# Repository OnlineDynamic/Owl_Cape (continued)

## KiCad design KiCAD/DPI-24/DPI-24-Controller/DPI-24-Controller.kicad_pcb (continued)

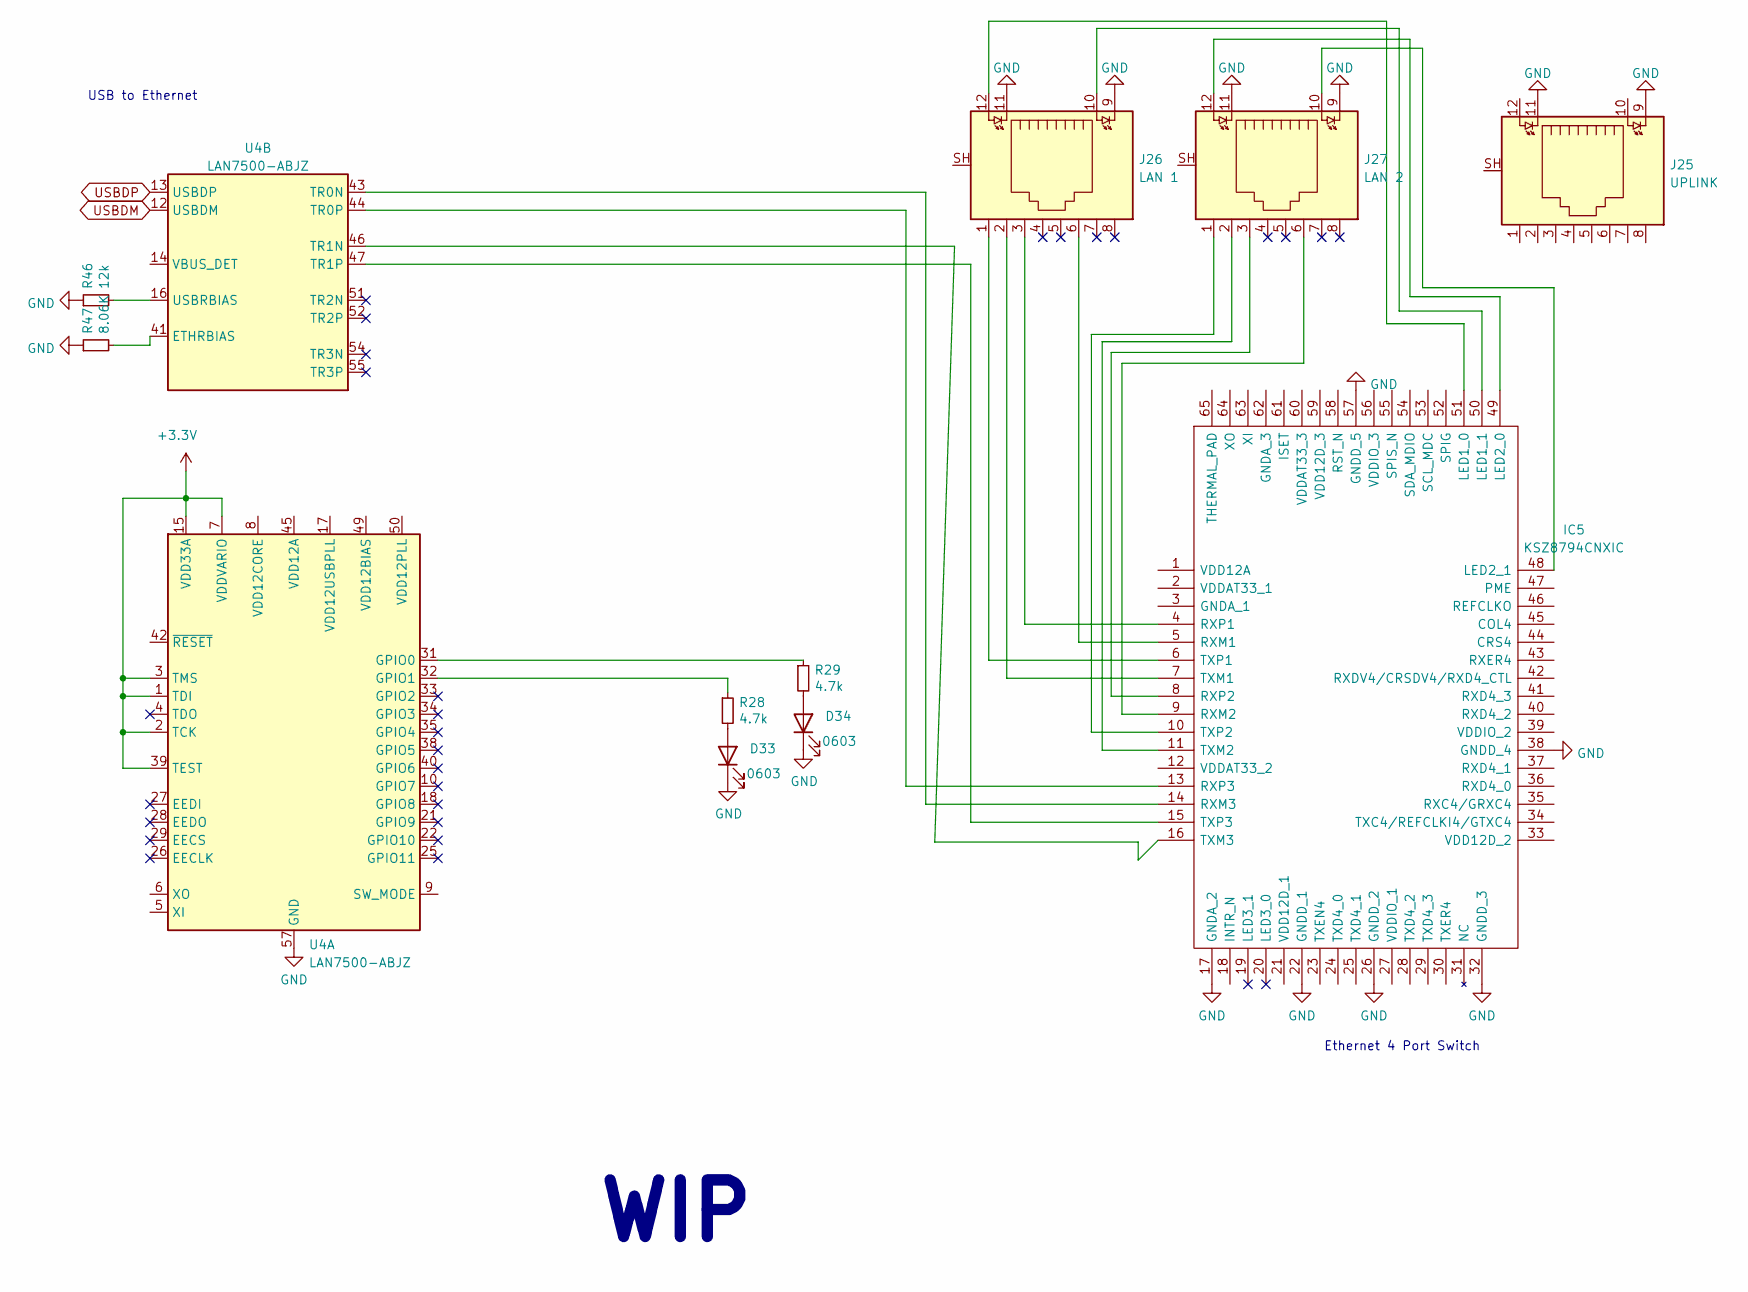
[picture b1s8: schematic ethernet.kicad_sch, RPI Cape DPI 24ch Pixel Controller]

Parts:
D33, D34: 0603; LED_0603_1608Metric
IC5: KSZ8794CNXIC; QFN40P800X800X90-65N; Mouser Part Number 998-KSZ8794CNXIC
J25: UPLINK; RJ45_BEL_SS74301-00x_Vertical
J26: LAN 1; RJ45_BEL_SS74301-00x_Vertical
J27: LAN 2; RJ45_BEL_SS74301-00x_Vertical
R28, R29: 4.7k; R_0805_2012Metric
R46: 12k; R_0805_2012Metric
R47: 8.06K; R_0805_2012Metric
U4: LAN7500-ABJZ; QFN-56-1EP_8x8mm_P0.5mm_EP5.9x5.9mm

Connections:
unnamed: D33.2 (A), R28.2
unnamed: D34.2 (A), R29.2
unnamed: IC5.4 (RXP1), J26.3
unnamed: IC5.5 (RXM1), J26.6
unnamed: IC5.6 (TXP1), J26.1
unnamed: IC5.7 (TXM1), J26.2
unnamed: IC5.8 (RXP2), J27.3
unnamed: IC5.9 (RXM2), J27.6
unnamed: IC5.10 (TXP2), J27.1
unnamed: IC5.11 (TXM2), J27.2
unnamed: IC5.13 (RXP3), U4.44 (TR0P)
unnamed: IC5.14 (RXM3), U4.43 (TR0N)
unnamed: IC5.15 (TXP3), U4.47 (TR1P)
unnamed: IC5.16 (TXM3), U4.46 (TR1N)
unnamed: IC5.48 (LED2_1), J27.10
unnamed: IC5.49 (LED2_0), J27.12
unnamed: IC5.50 (LED1_1), J26.10
unnamed: IC5.51 (LED1_0), J26.12
unnamed: R28.1, U4.32 (GPIO1)
unnamed: R29.1, U4.31 (GPIO0)
unnamed: R46.2, U4.16 (USBRBIAS)
unnamed: R47.2, U4.41 (ETHRBIAS)
unnamed: U4.8 (VDD12CORE), U4.11 (VDD12CORE), U4.20 (VDD12CORE), U4.23 (VDD12CORE), U4.30 (VDD12CORE), U4.36 (VDD12CORE)
unnamed: U4.45 (VDD12A), U4.48 (VDD12A), U4.53 (VDD12A), U4.56 (VDD12A)
USBDM: U4.12 (USBDM)
USBDP: U4.13 (USBDP)

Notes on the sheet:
USB to Ethernet
Ethernet 4 Port Switch
WIP

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
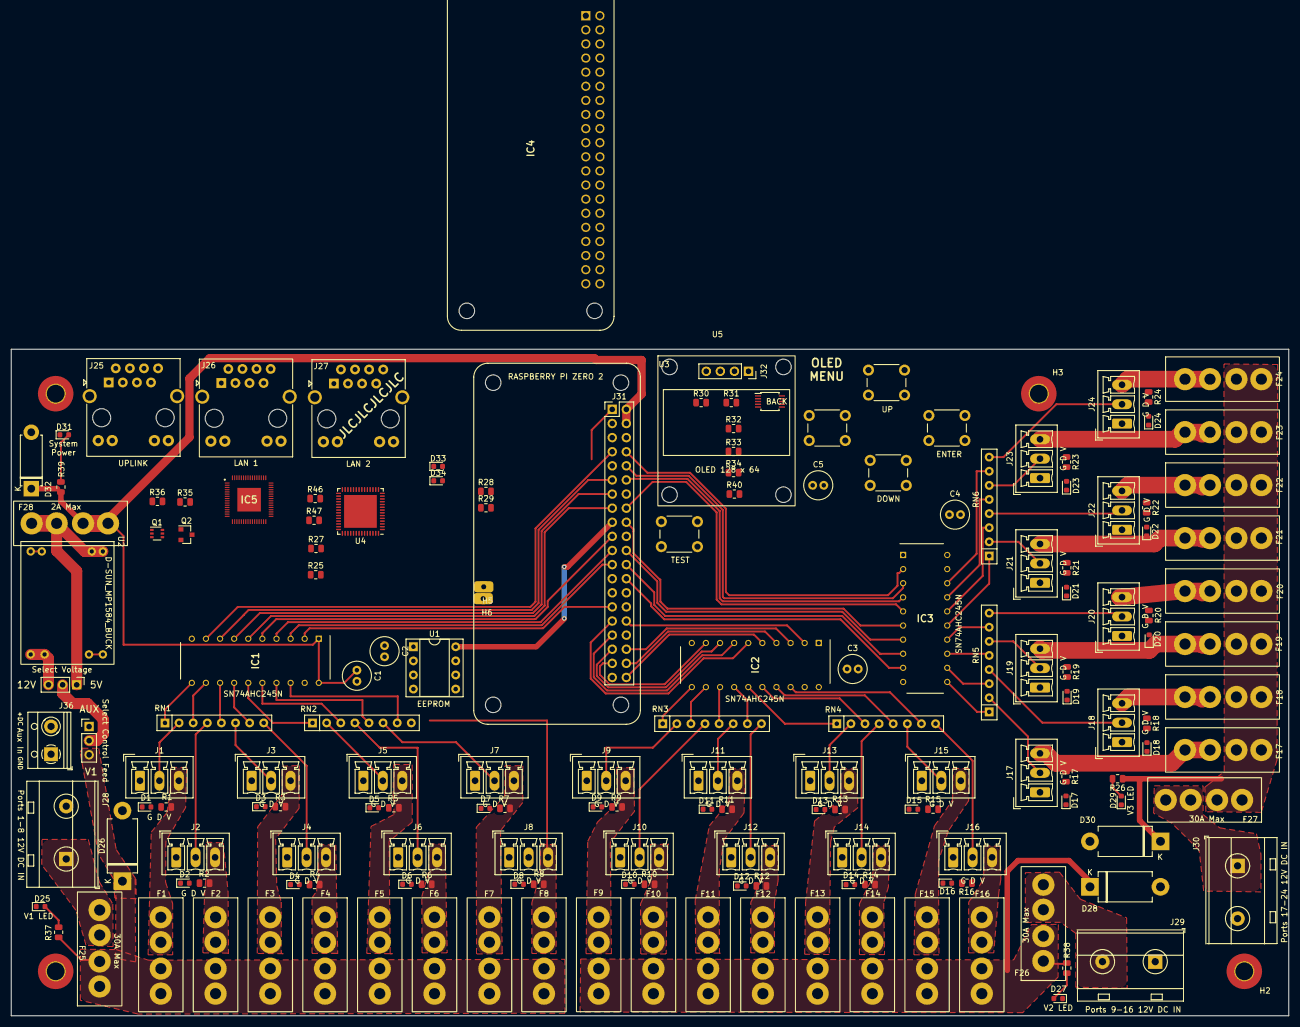
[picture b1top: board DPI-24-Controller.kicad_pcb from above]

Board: 2 copper layers, 230.0 x 120.0 mm, 173 parts (0 on the bottom side), 176 nets.

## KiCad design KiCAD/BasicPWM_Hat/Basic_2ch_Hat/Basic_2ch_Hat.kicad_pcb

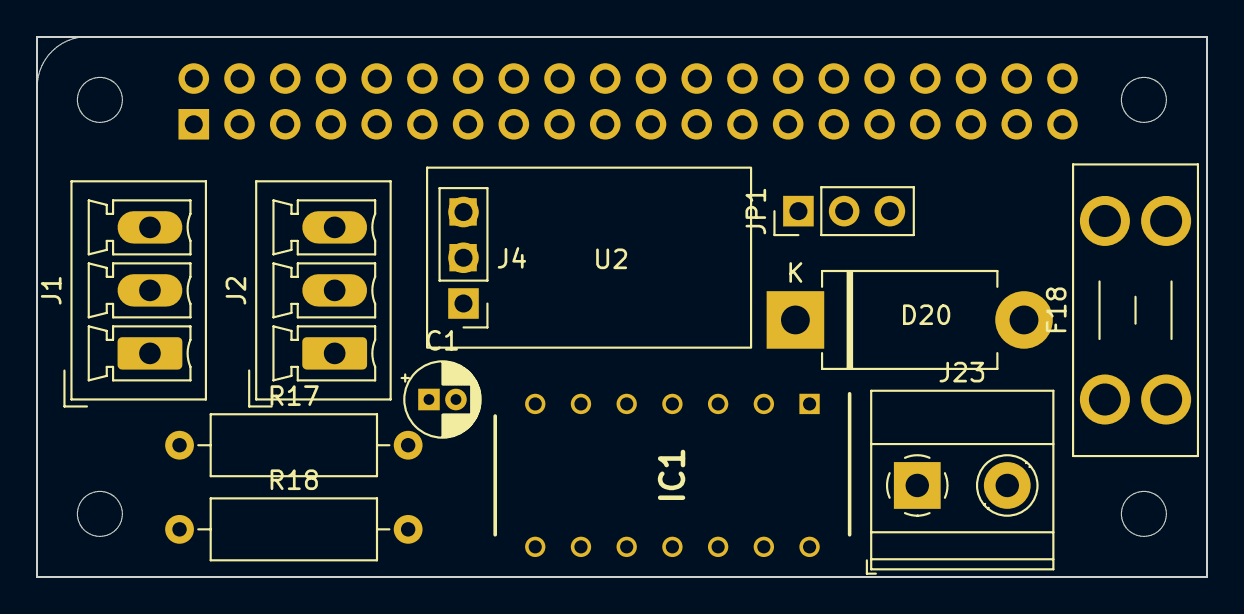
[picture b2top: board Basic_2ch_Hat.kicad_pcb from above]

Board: 2 copper layers, 65.0 x 30.0 mm, 17 parts (1 on the bottom side), 13 nets, no tracks yet.

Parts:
C1: 0.1uF; CP_Radial_D4.0mm_P1.50mm
D20: SB5100; D_DO-201AD_P12.70mm_Horizontal
F18: 30A Max; Fuseholder_Blade_Mini_Keystone_3568
H1, H2, H3, H4: MountingHole; MountingHole_2.5mm
IC1: SN74HC126N; DIP794W53P254L1930H508Q14N
J1, J2: G D V; PhoenixContact_MCV_1,5_3-G-3.5_1x03_P3.50mm_Vertical
J3: Conn_02x20_Odd_Even_MountingPin; PinSocket_2x20_P2.54mm_Vertical
J4: Conn_01x03; PinHeader_1x03_P2.54mm_Vertical
J23: DC In; TerminalBlock_Phoenix_MKDS-1,5-2_1x02_P5.00mm_Horizontal
JP1: 5V / 12V; PinHeader_1x03_P2.54mm_Vertical
R17, R18: 33; R_Axial_DIN0309_L9.0mm_D3.2mm_P12.70mm_Horizontal
U2: DC DC_BUCK Module; DC DC BUCK MODULE

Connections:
+3V3: J3.1, J3.17
+5V: C1.1, IC1.14 (VCC)
DATA1: IC1.2 (1A), J3.32
DATA2: IC1.5 (2A), J3.33
GND: C1.2, D20.2 (A), IC1.1 (1OE), IC1.4 (2OE), IC1.7 (GND), IC1.10 (3OE), IC1.13 (4OE), J1.1, J2.1, J3.6, J3.9, J3.14, J3.20, J3.25, J3.30, J3.34, J3.39, J4.2, J23.1
unnamed: IC1.3 (1Y), R18.2
unnamed: IC1.6 (2Y), R17.2
unnamed: J1.2, R18.1
unnamed: J2.2, R17.1
V1: F18.1, J23.2
V5: J3.2, J3.4, J4.3, JP1.1 (A)
V12: J4.1, JP1.3 (B)
VIN1: D20.1 (K), F18.2, J1.3, J2.3, JP1.2 (C)

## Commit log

2022-03-18 typos
2022-03-18 inital commit of KiCAD WIP
2022-03-18 upload
2022-03-18 research upload
2022-03-18 updates to power components
2022-03-20 logo and kicad updates
2022-03-24 updates and eeprom settings
2022-03-24 instructions for eepromprogramming
2022-03-24 minor format updates
2022-03-24 added pinout table
2022-03-24 update pinout table
2022-03-24 footnote update
2022-03-24 renamed file
2022-03-25 minor readme updates
2022-03-27 added buck and pi
2022-03-28 started routing cu
2022-04-03 swap chips to better speed / layout
2022-04-05 major update to layout
2022-04-17 formatting fix
2022-04-20 updates based on testing
2022-04-24 addition of DPI-24 model
2022-04-24 dpi-24 updates
2022-04-25 layout updates
2022-04-25 pcb layout changes
2022-04-25 further layout updates
2022-04-25 more layout
2022-04-28 more layout tweaking and a bit of copper!
2022-04-29 more tweaks
